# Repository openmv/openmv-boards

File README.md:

# openmv-boards
OpenMV boards, schematics, and layout.

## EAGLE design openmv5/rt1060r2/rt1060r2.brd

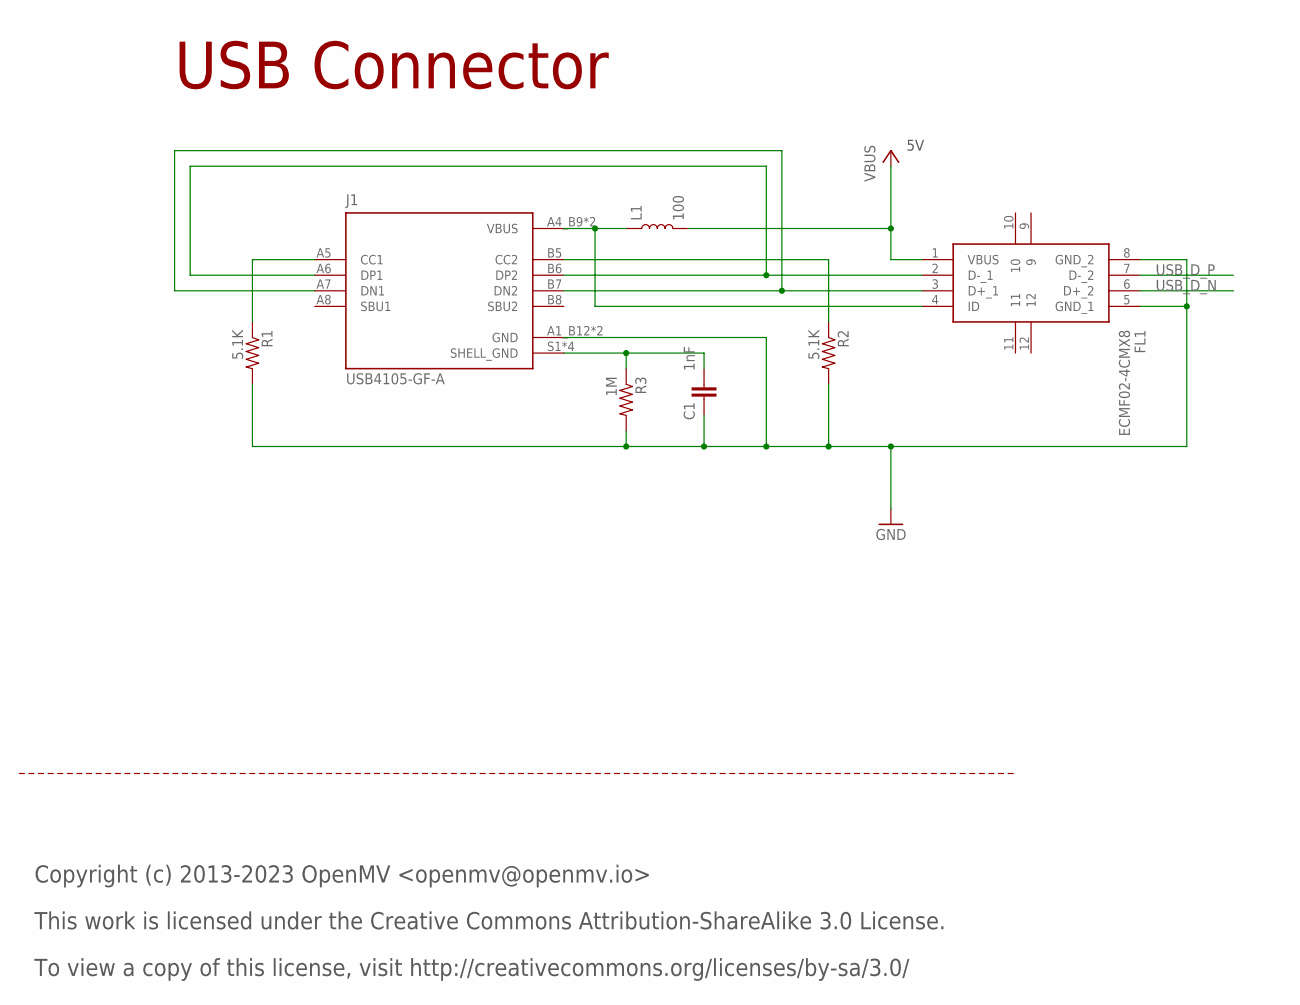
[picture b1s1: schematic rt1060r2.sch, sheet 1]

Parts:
C1: 1nF; 0402; MPN VJ0402Y102JXACW1BC
FL1: ECMF02-4CMX8; ECMF024CMX8; MPN ECMF02-4CMX8
J1: USB4105-GF-A; GCT_USB4105-GF-A; MPN USB4105-GF-A
L1: 100; 0603; MPN MFBM1V1608-101-R
R1, R2: 5.1K; 0402; MPN RC0402JR-075K1L
R3: 1M; 0402; MPN CRCW04021M00FKEDC

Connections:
CC1: J1.A5 (CC1), R1.1
CC2: J1.B5 (CC2), R2.1
D_N: FL1.3 (D+_1), J1.A7 (DN1), J1.B7 (DN2)
D_P: FL1.2 (D-_1), J1.A6 (DP1), J1.B6 (DP2)
GND: C1.1, FL1.5 (GND_1), FL1.8 (GND_2), J1.A1_B12 (GND), J1.B1_A12 (GND), R1.2, R2.2, R3.2; also elsewhere on the board
SHELL_GND: C1.2, J1.S1 (SHELL_GND), J1.S2 (SHELL_GND), J1.S3 (SHELL_GND), J1.S4 (SHELL_GND), R3.1
USB_D_N: FL1.6 (D+_2); also elsewhere on the board
USB_D_P: FL1.7 (D-_2); also elsewhere on the board
USB_VBUS: FL1.4 (ID), J1.A4_B9 (VBUS), J1.B4_A9 (VBUS), L1.1
VBUS: FL1.1 (VBUS), L1.2; also elsewhere on the board

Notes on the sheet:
USB Connector
Copyright (c) 2013-2023 OpenMV <openmv@openmv.io>
This work is licensed under the Creative Commons Attribution-ShareAlike 3.0 License.
To view a copy of this license, visit http://creativecommons.org/licenses/by-sa/3.0/

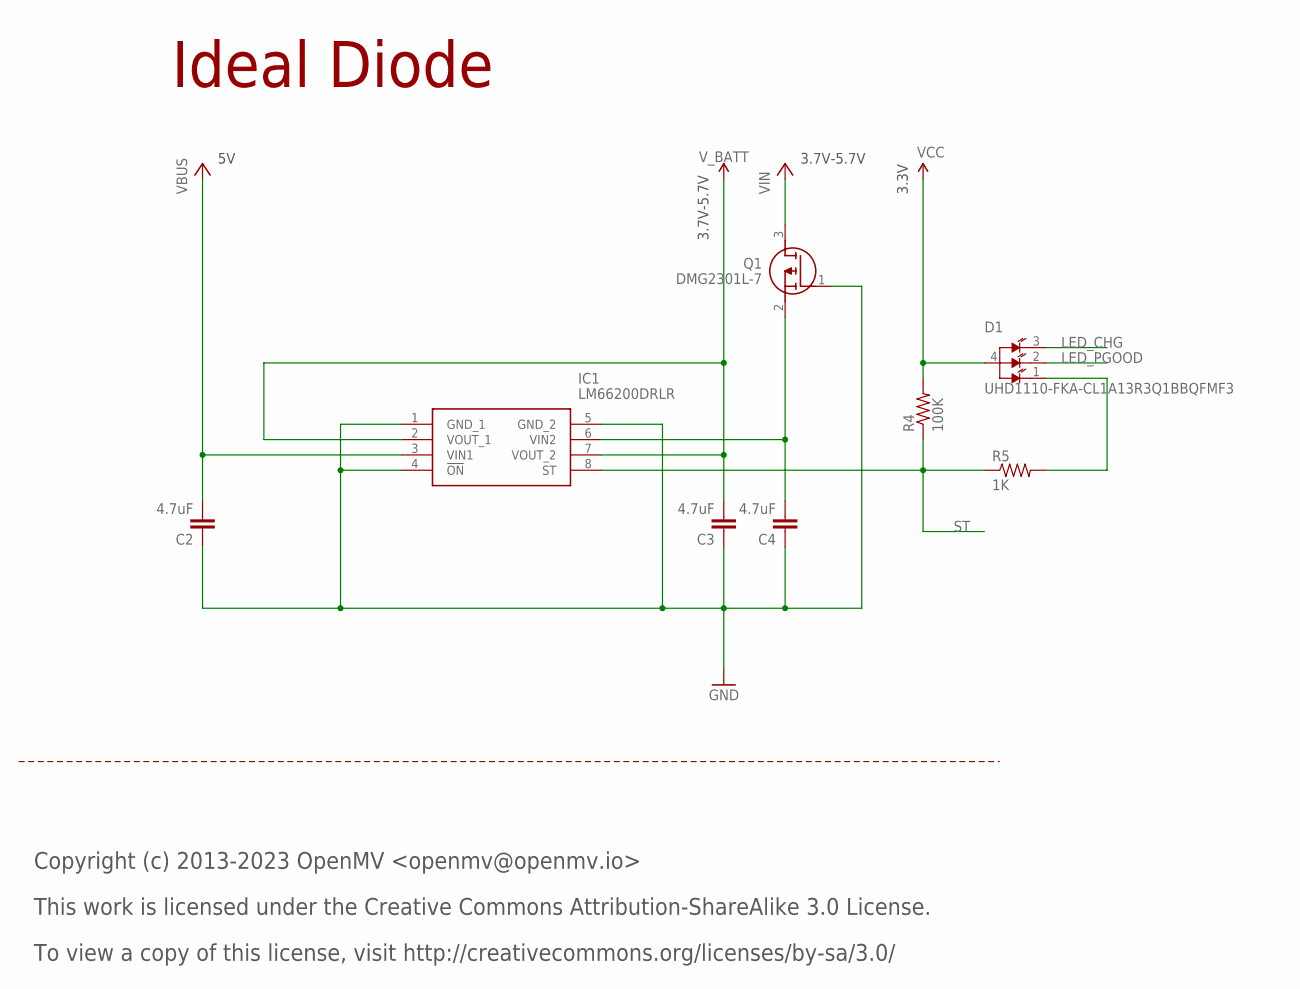
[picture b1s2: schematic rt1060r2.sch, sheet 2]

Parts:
C2, C3, C4: 4.7uF; 0402; MPN JMK105BBJ475MV-F
D1: UHD1110-FKA-CL1A13R3Q1BBQFMF3; LED_UHD1110-FKA-CL1A13R3Q1BBQFMF3; MPN UHD1110-FKA-CL1A13r3q1BBQFMF3
IC1: LM66200DRLR; SOTFL50P160X60-8N; MPN LM66200DRLR
Q1: DMG2301L-7; SOT96P240X110-3N; MPN DMG2301L-7
R4: 100K; 0402; MPN AC0402FR-07100KL
R5: 1K; 0402; MPN CRCW04021K00FKEDC

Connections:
GND: C2.1, C3.1, C4.1, IC1.1 (GND_1), IC1.4 (!ON), IC1.5 (GND_2), Q1.1 (G); also elsewhere on the board
LED_CHG: D1.3 (RED); also elsewhere on the board
LED_PGOOD: D1.2 (GREEN); also elsewhere on the board
LED_ST: D1.1 (BLUE), R5.2
ST: IC1.8 (ST), R4.1, R5.1; also elsewhere on the board
VBUS: C2.2, IC1.3 (VIN1); also elsewhere on the board
VCC: D1.4 (ANODE), R4.2; also elsewhere on the board
VIN: Q1.3 (D); also elsewhere on the board
VIN_INT: C4.2, IC1.6 (VIN2), Q1.2 (S)
V_BATT: C3.2, IC1.2 (VOUT_1), IC1.7 (VOUT_2); also elsewhere on the board

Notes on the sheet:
Copyright (c) 2013-2023 OpenMV <openmv@openmv.io>
This work is licensed under the Creative Commons Attribution-ShareAlike 3.0 License.
To view a copy of this license, visit http://creativecommons.org/licenses/by-sa/3.0/
Ideal Diode
3.7V-5.7V
3.3V

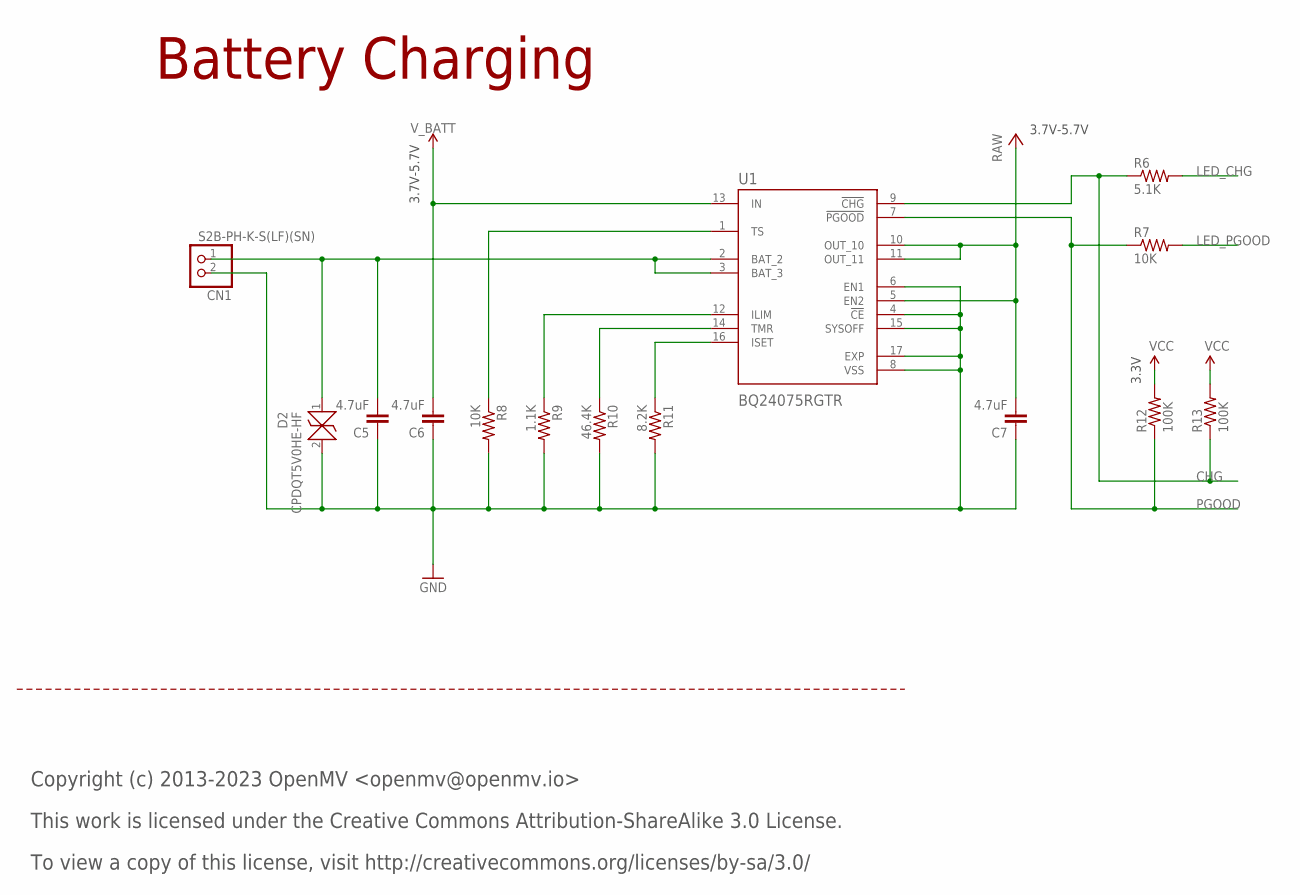
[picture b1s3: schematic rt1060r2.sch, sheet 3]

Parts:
C5, C6, C7: 4.7uF; 0402; MPN JMK105BBJ475MV-F
CN1: S2B-PH-K-S(LF)(SN); JST-PH-2-THM-RA; MPN S2B-PH-K-S(LF)(SN)
D2: CPDQT5V0HE-HF; CPDQT5V0HEHF; MPN CPDQT5V0HE-HF
R6: 5.1K; 0402; MPN RC0402JR-075K1L
R7, R8: 10K; 0402; MPN AC0402FR-1310KL
R9: 1.1K; 0402; MPN RC0402JR-071K1L
R10: 46.4K; 0402; MPN WR04X4642FTL
R11: 8.2K; 0402; MPN CR0402-FX-8201GLF
R12, R13: 100K; 0402; MPN AC0402FR-07100KL
U1: BQ24075RGTR; QFN50P300X300X100-17N; MPN BQ24075RGTR

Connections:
BAT: C5.2, CN1.1 (2), D2.1, U1.2 (BAT_2), U1.3 (BAT_3)
CHG: R6.1, R13.1, U1.9 (!CHG); also elsewhere on the board
GND: C5.1, C6.1, C7.1, CN1.2 (1), D2.2, R8.2, R9.2, R10.2, R11.2, U1.4 (!CE), U1.6 (EN1), U1.8 (VSS), U1.15 (SYSOFF), U1.17 (EXP); also elsewhere on the board
ILIM: R9.1, U1.12 (ILIM)
ISET: R11.1, U1.16 (ISET)
LED_CHG: R6.2; also elsewhere on the board
LED_PGOOD: R7.2; also elsewhere on the board
PGOOD: R7.1, R12.1, U1.7 (!PGOOD); also elsewhere on the board
RAW: C7.2, U1.5 (EN2), U1.10 (OUT_10), U1.11 (OUT_11); also elsewhere on the board
TMR: R10.1, U1.14 (TMR)
TS: R8.1, U1.1 (TS)
VCC: R12.2, R13.2; also elsewhere on the board
V_BATT: C6.2, U1.13 (IN); also elsewhere on the board

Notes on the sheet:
Copyright (c) 2013-2023 OpenMV <openmv@openmv.io>
This work is licensed under the Creative Commons Attribution-ShareAlike 3.0 License.
To view a copy of this license, visit http://creativecommons.org/licenses/by-sa/3.0/
Battery Charging
3.7V-5.7V
3.3V

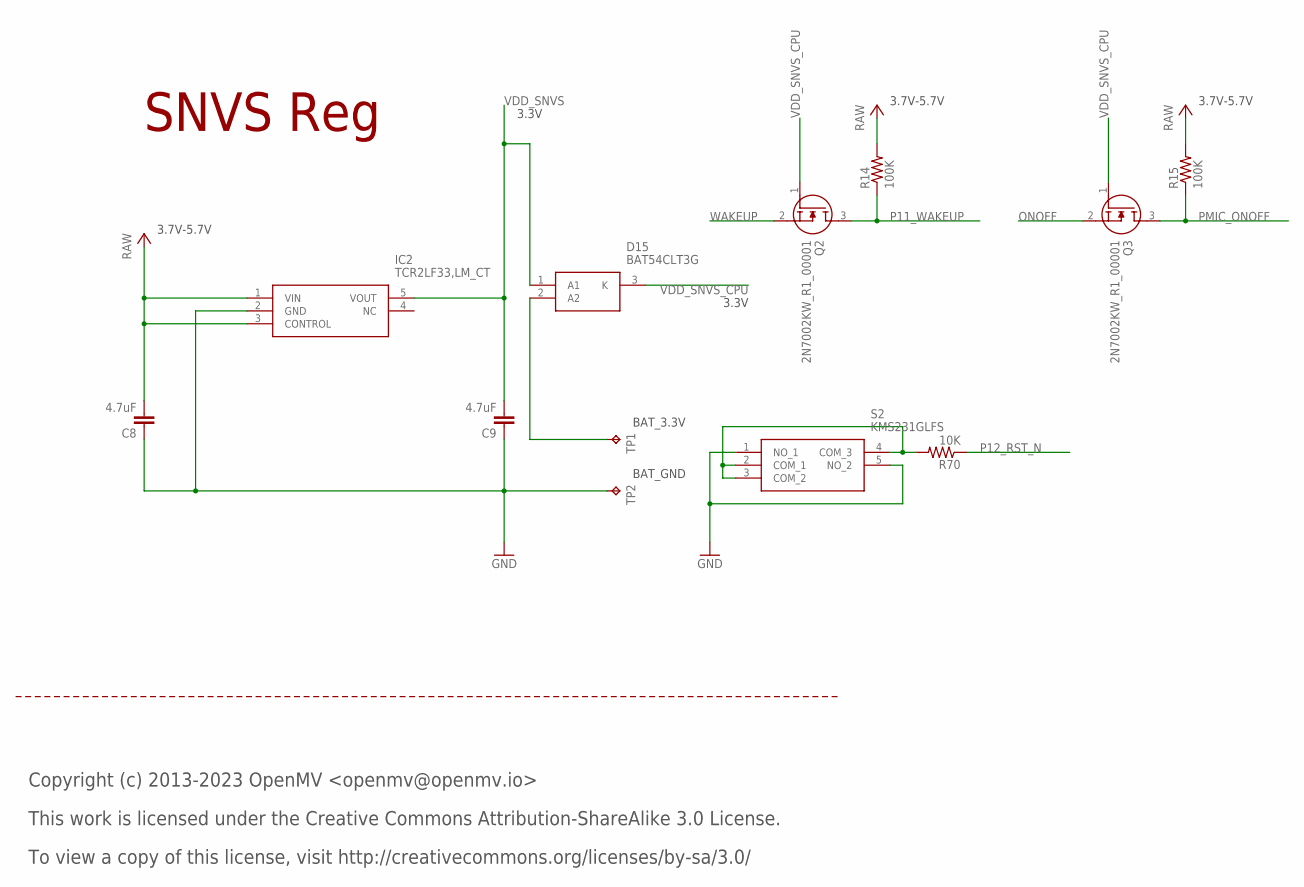
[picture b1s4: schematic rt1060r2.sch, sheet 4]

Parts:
C8, C9: 4.7uF; 0402; MPN JMK105BBJ475MV-F
D15: BAT54CLT3G; SOT96P237X111-3N
IC2: TCR2LF33,LM_CT; TCR2LF33LMCT; MPN TCR2LF33,LM(CT
Q2, Q3: 2N7002KW_R1_00001; SOT65P210X110-3N; MPN 2N7002KW_R1_00001
R14, R15: 100K; 0402; MPN AC0402FR-07100KL
R70: 10K; 0402; MPN AC0402FR-1310KL
S2: KMS231GLFS; MPN KMS231GLFS
TP1, TP2: TPTP10R; TP10R

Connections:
GND: C8.1, C9.1, IC2.2 (GND), S2.1 (NO_1), S2.5 (NO_2), TP2.TP; also elsewhere on the board
ONOFF: Q3.2 (S); also elsewhere on the board
P11_WAKEUP: Q2.3 (D), R14.1; also elsewhere on the board
P12_RST_N: R70.1; also elsewhere on the board
PMIC_ONOFF: Q3.3 (D), R15.1; also elsewhere on the board
RAW: C8.2, IC2.1 (VIN), IC2.3 (CONTROL), R14.2, R15.2; also elsewhere on the board
RST_BUTTON: R70.2, S2.2 (COM_1), S2.3 (COM_2), S2.4 (COM_3)
SNVS_BAT: D15.2 (A2), TP1.TP
VDD_SNVS: C9.2, D15.1 (A1), IC2.5 (VOUT)
VDD_SNVS_CPU: D15.3 (K), Q2.1 (G), Q3.1 (G); also elsewhere on the board
WAKEUP: Q2.2 (S); also elsewhere on the board

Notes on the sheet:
Copyright (c) 2013-2023 OpenMV <openmv@openmv.io>
This work is licensed under the Creative Commons Attribution-ShareAlike 3.0 License.
To view a copy of this license, visit http://creativecommons.org/licenses/by-sa/3.0/
SNVS Reg
3.7V-5.7V
3.3V
BAT_3.3V
BAT_GND

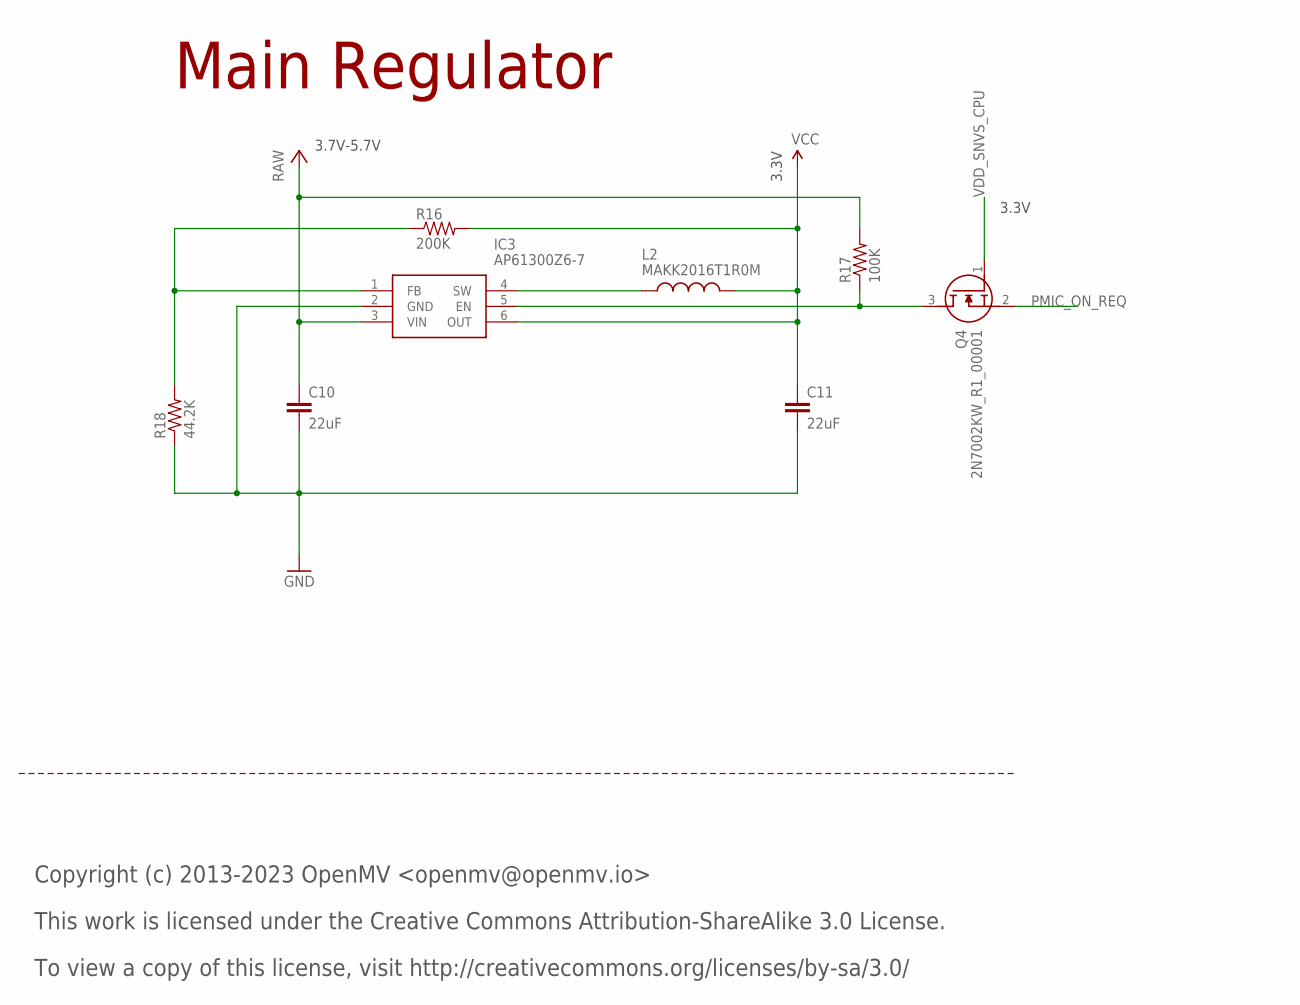
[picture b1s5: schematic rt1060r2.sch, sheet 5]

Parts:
C10, C11: 22uF; 0805; MPN CL21A226MQQNNNE
IC3: AP61300Z6-7; SOTFL50P162X60-6N; MPN AP61300Z6-7
L2: MAKK2016T1R0M; INDC2016X100N; MPN MAKK2016T1R0M
Q4: 2N7002KW_R1_00001; SOT65P210X110-3N; MPN 2N7002KW_R1_00001
R16: 200K; 0402; MPN CRCW0402200KFKEDC
R17: 100K; 0402; MPN AC0402FR-07100KL
R18: 44.2K; 0402; MPN AC0402FR-0744K2L

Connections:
EN: IC3.5 (EN), Q4.3 (D), R17.1
FB: IC3.1 (FB), R16.1, R18.2
GND: C10.2, C11.2, IC3.2 (GND), R18.1; also elsewhere on the board
PMIC_ON_REQ: Q4.2 (S); also elsewhere on the board
RAW: C10.1, IC3.3 (VIN), R17.2; also elsewhere on the board
SW: IC3.4 (SW), L2.1
VCC: C11.1, IC3.6 (OUT), L2.2, R16.2; also elsewhere on the board
VDD_SNVS_CPU: Q4.1 (G); also elsewhere on the board

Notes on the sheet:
Copyright (c) 2013-2023 OpenMV <openmv@openmv.io>
This work is licensed under the Creative Commons Attribution-ShareAlike 3.0 License.
To view a copy of this license, visit http://creativecommons.org/licenses/by-sa/3.0/
Main Regulator
3.7V-5.7V
3.3V

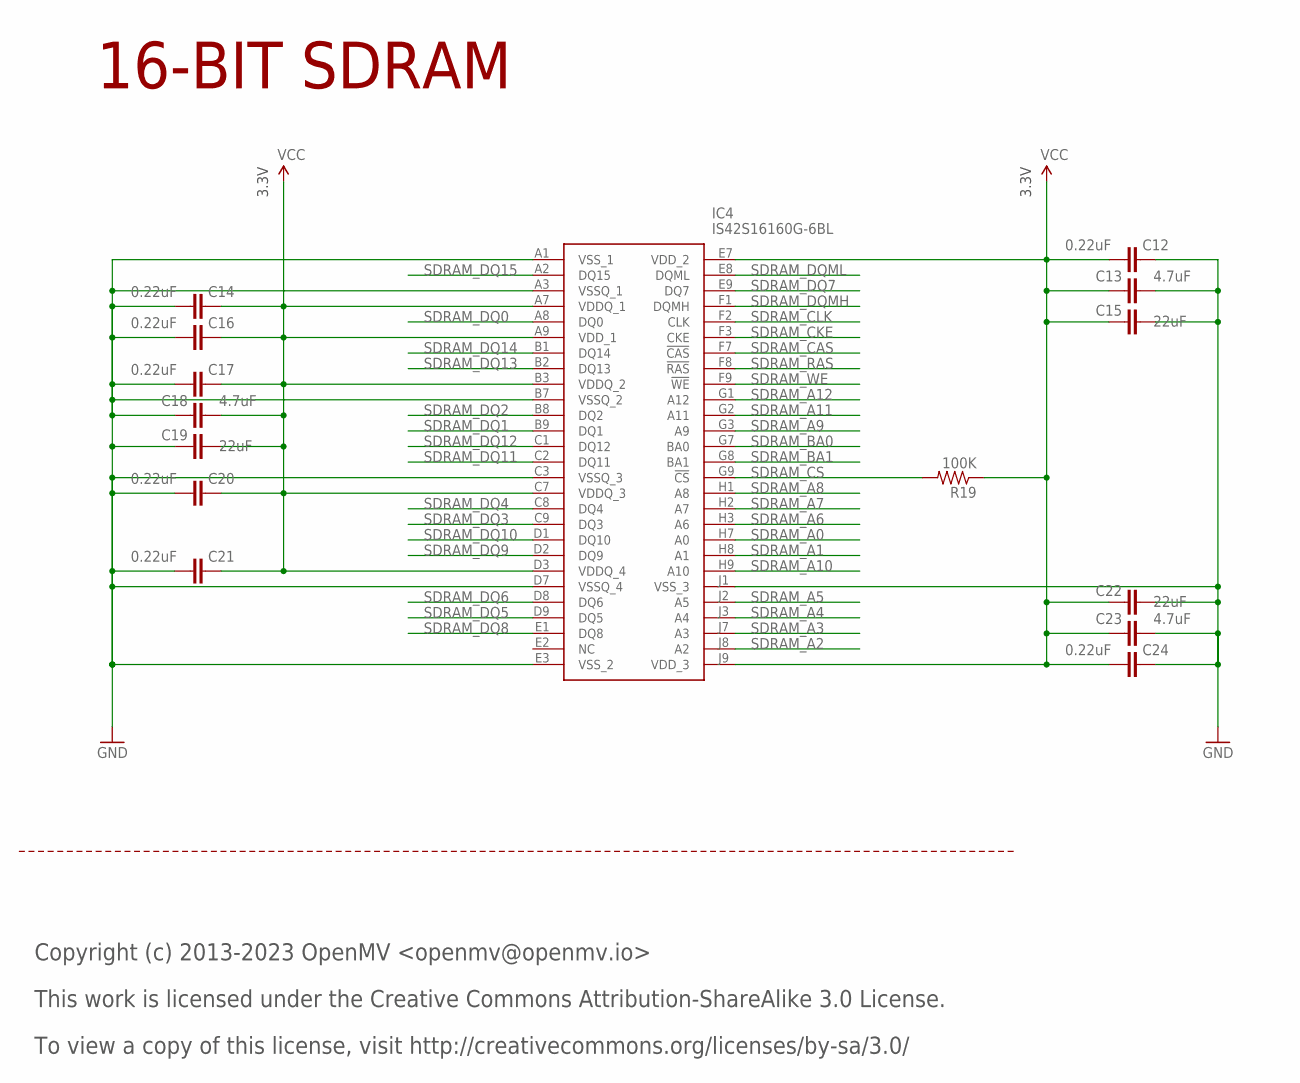
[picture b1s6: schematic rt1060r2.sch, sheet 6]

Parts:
C12, C14, C16, C17, C20, C21, C24: 0.22uF; C0201; MPN GRM033R60J224ME15D
C13, C18, C23: 4.7uF; 0402; MPN JMK105BBJ475MV-F
C15, C19, C22: 22uF; 0805; MPN CL21A226MQQNNNE
IC4: IS42S16160G-6BL; BGA54C80P9X9_800X800X120; MPN IS42S16160G-6BL
R19: 100K; 0402; MPN AC0402FR-07100KL

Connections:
GND: C12.1, C13.2, C14.2, C15.2, C16.2, C17.2, C18.1, C19.1, C20.2, C21.2, C22.2, C23.2, C24.1, IC4.A1 (VSS_1), IC4.A3 (VSSQ_1), IC4.B7 (VSSQ_2), IC4.C3 (VSSQ_3), IC4.D7 (VSSQ_4), IC4.E3 (VSS_2), IC4.J1 (VSS_3); also elsewhere on the board
SDRAM_A0: IC4.H7 (A0); also elsewhere on the board
SDRAM_A1: IC4.H8 (A1); also elsewhere on the board
SDRAM_A2: IC4.J8 (A2); also elsewhere on the board
SDRAM_A3: IC4.J7 (A3); also elsewhere on the board
SDRAM_A4: IC4.J3 (A4); also elsewhere on the board
SDRAM_A5: IC4.J2 (A5); also elsewhere on the board
SDRAM_A6: IC4.H3 (A6); also elsewhere on the board
SDRAM_A7: IC4.H2 (A7); also elsewhere on the board
SDRAM_A8: IC4.H1 (A8); also elsewhere on the board
SDRAM_A9: IC4.G3 (A9); also elsewhere on the board
SDRAM_A10: IC4.H9 (A10); also elsewhere on the board
SDRAM_A11: IC4.G2 (A11); also elsewhere on the board
SDRAM_A12: IC4.G1 (A12); also elsewhere on the board
SDRAM_BA0: IC4.G7 (BA0); also elsewhere on the board
SDRAM_BA1: IC4.G8 (BA1); also elsewhere on the board
SDRAM_CAS: IC4.F7 (!CAS); also elsewhere on the board
SDRAM_CKE: IC4.F3 (CKE); also elsewhere on the board
SDRAM_CLK: IC4.F2 (CLK); also elsewhere on the board
SDRAM_CS: IC4.G9 (!CS), R19.2; also elsewhere on the board
SDRAM_DQ0: IC4.A8 (DQ0); also elsewhere on the board
SDRAM_DQ1: IC4.B9 (DQ1); also elsewhere on the board
SDRAM_DQ2: IC4.B8 (DQ2); also elsewhere on the board
SDRAM_DQ3: IC4.C9 (DQ3); also elsewhere on the board
SDRAM_DQ4: IC4.C8 (DQ4); also elsewhere on the board
SDRAM_DQ5: IC4.D9 (DQ5); also elsewhere on the board
SDRAM_DQ6: IC4.D8 (DQ6); also elsewhere on the board
SDRAM_DQ7: IC4.E9 (DQ7); also elsewhere on the board
SDRAM_DQ8: IC4.E1 (DQ8); also elsewhere on the board
SDRAM_DQ9: IC4.D2 (DQ9); also elsewhere on the board
SDRAM_DQ10: IC4.D1 (DQ10); also elsewhere on the board
SDRAM_DQ11: IC4.C2 (DQ11); also elsewhere on the board
SDRAM_DQ12: IC4.C1 (DQ12); also elsewhere on the board
SDRAM_DQ13: IC4.B2 (DQ13); also elsewhere on the board
SDRAM_DQ14: IC4.B1 (DQ14); also elsewhere on the board
SDRAM_DQ15: IC4.A2 (DQ15); also elsewhere on the board
SDRAM_DQMH: IC4.F1 (DQMH); also elsewhere on the board
SDRAM_DQML: IC4.E8 (DQML); also elsewhere on the board
SDRAM_RAS: IC4.F8 (!RAS); also elsewhere on the board
SDRAM_WE: IC4.F9 (!WE); also elsewhere on the board
VCC: C12.2, C13.1, C14.1, C15.1, C16.1, C17.1, C18.2, C19.2, C20.1, C21.1, C22.1, C23.1, C24.2, IC4.A7 (VDDQ_1), IC4.A9 (VDD_1), IC4.B3 (VDDQ_2), IC4.C7 (VDDQ_3), IC4.D3 (VDDQ_4), IC4.E7 (VDD_2), IC4.J9 (VDD_3), R19.1; also elsewhere on the board

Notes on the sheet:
Copyright (c) 2013-2023 OpenMV <openmv@openmv.io>
This work is licensed under the Creative Commons Attribution-ShareAlike 3.0 License.
To view a copy of this license, visit http://creativecommons.org/licenses/by-sa/3.0/
16-BIT SDRAM
3.3V

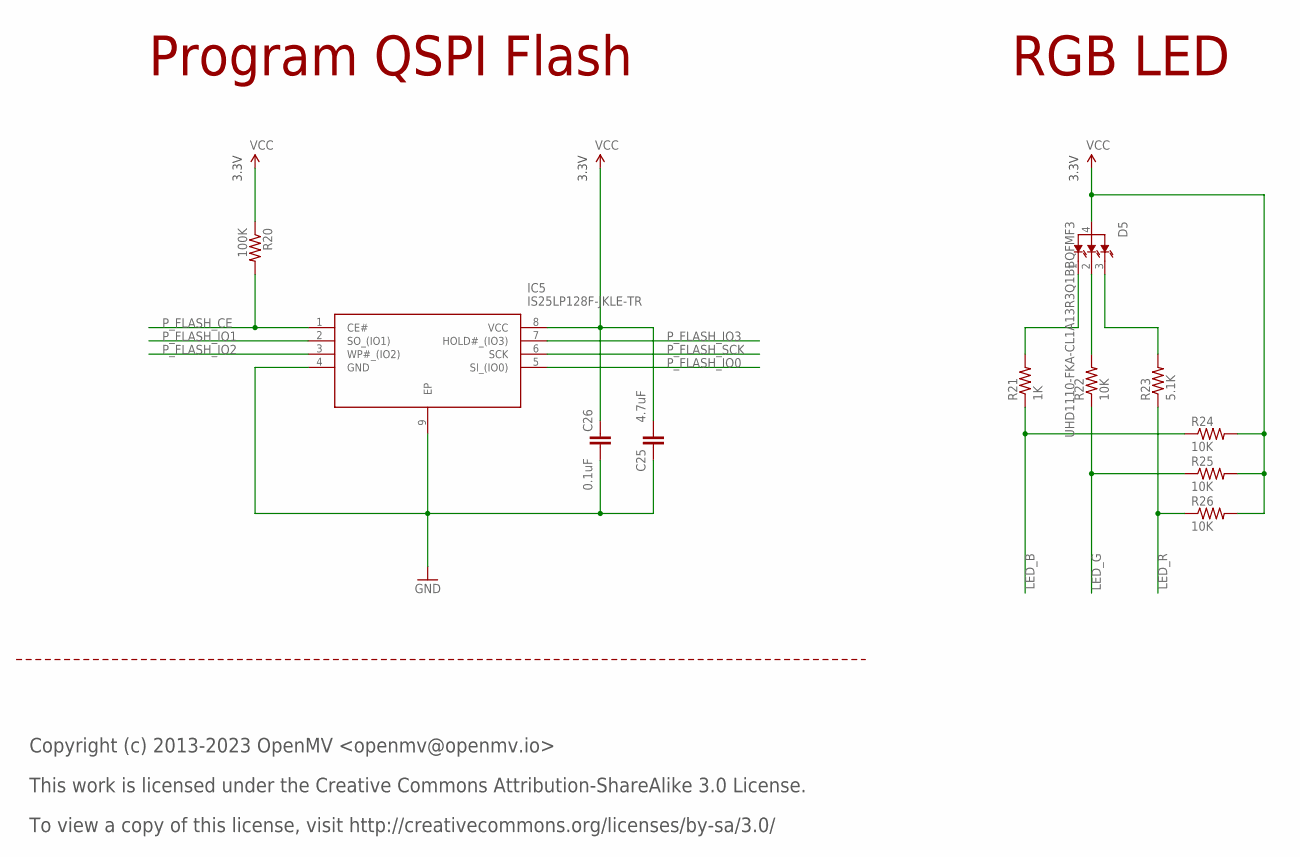
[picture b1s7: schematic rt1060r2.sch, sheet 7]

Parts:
C25: 4.7uF; 0402; MPN JMK105BBJ475MV-F
C26: 0.1uF; 0402; MPN C0402C104Z4VAC
D5: UHD1110-FKA-CL1A13R3Q1BBQFMF3; LED_UHD1110-FKA-CL1A13R3Q1BBQFMF3; MPN UHD1110-FKA-CL1A13r3q1BBQFMF3
IC5: IS25LP128F-JKLE-TR; SON127P500X595X80-9N; MANUFACTURER_PART_NUMBER IS25LP128F-JKLE-TR; MOUSER_PART_NUMBER 870-5LP128F-JKLE-TR
R20: 100K; 0402; MPN AC0402FR-07100KL
R21: 1K; 0402; MPN CRCW04021K00FKEDC
R22, R24, R25, R26: 10K; 0402; MPN AC0402FR-1310KL
R23: 5.1K; 0402; MPN RC0402JR-075K1L

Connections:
GND: C25.1, C26.2, IC5.4 (GND), IC5.9 (EP); also elsewhere on the board
LED_B: R21.1, R24.1; also elsewhere on the board
LED_B_INT: D5.1 (BLUE), R21.2
LED_G: R22.1, R25.1; also elsewhere on the board
LED_G_INT: D5.2 (GREEN), R22.2
LED_R: R23.1, R26.1; also elsewhere on the board
LED_R_INT: D5.3 (RED), R23.2
P_FLASH_CE: IC5.1 (CE#), R20.2; also elsewhere on the board
P_FLASH_IO0: IC5.5 (SI_(IO0)); also elsewhere on the board
P_FLASH_IO1: IC5.2 (SO_(IO1)); also elsewhere on the board
P_FLASH_IO2: IC5.3 (WP#_(IO2)); also elsewhere on the board
P_FLASH_IO3: IC5.7 (HOLD#_(IO3)); also elsewhere on the board
P_FLASH_SCK: IC5.6 (SCK); also elsewhere on the board
VCC: C25.2, C26.1, D5.4 (ANODE), IC5.8 (VCC), R20.1, R24.2, R25.2, R26.2; also elsewhere on the board

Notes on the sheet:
Copyright (c) 2013-2023 OpenMV <openmv@openmv.io>
This work is licensed under the Creative Commons Attribution-ShareAlike 3.0 License.
To view a copy of this license, visit http://creativecommons.org/licenses/by-sa/3.0/
Program QSPI Flash
RGB LED
3.3V

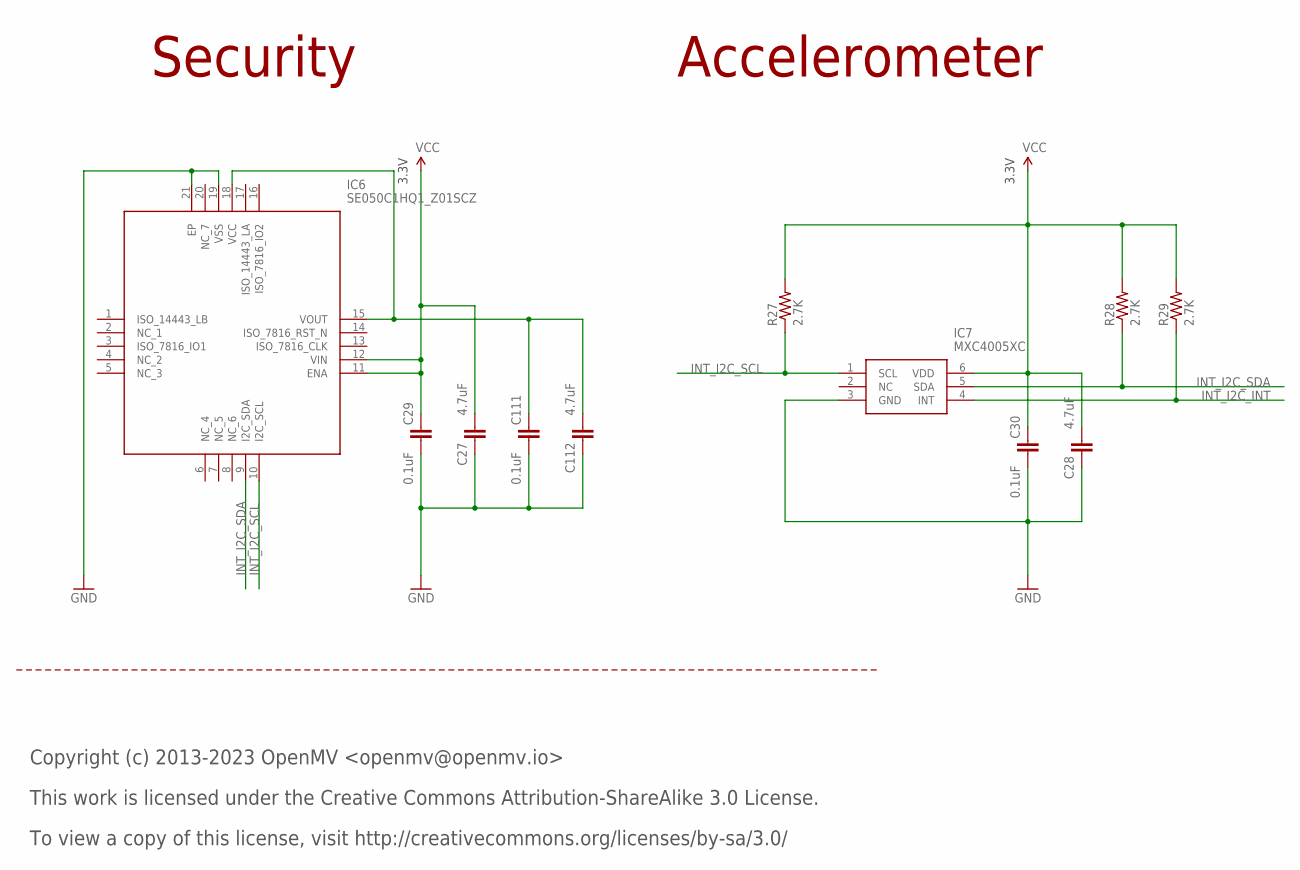
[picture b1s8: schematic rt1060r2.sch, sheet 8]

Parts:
C27, C28, C112: 4.7uF; 0402; MPN JMK105BBJ475MV-F
C29, C30, C111: 0.1uF; 0402; MPN C0402C104Z4VAC
IC6: SE050C1HQ1_Z01SCZ; QFN40P300X300X33-21N; MPN SE050C1HQ1/Z01SCZ
IC7: MXC4005XC; MPN MXC4005XC
R27, R28, R29: 2.7K; 0402; MPN AC0402JR-072K7L

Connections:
C_VOUT: C111.1, C112.2, IC6.15 (VOUT), IC6.18 (VCC)
GND: C27.1, C28.1, C29.2, C30.2, C111.2, C112.1, IC6.19 (VSS), IC6.21 (EP), IC7.3 (GND); also elsewhere on the board
INT_I2C_INT: IC7.4 (INT), R29.1; also elsewhere on the board
INT_I2C_SCL: IC6.10 (I2C_SCL), IC7.1 (SCL), R27.1; also elsewhere on the board
INT_I2C_SDA: IC6.9 (I2C_SDA), IC7.5 (SDA), R28.1; also elsewhere on the board
VCC: C27.2, C28.2, C29.1, C30.1, IC6.11 (ENA), IC6.12 (VIN), IC7.6 (VDD), R27.2, R28.2, R29.2; also elsewhere on the board

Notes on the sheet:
Copyright (c) 2013-2023 OpenMV <openmv@openmv.io>
This work is licensed under the Creative Commons Attribution-ShareAlike 3.0 License.
To view a copy of this license, visit http://creativecommons.org/licenses/by-sa/3.0/
Security
Accelerometer
3.3V

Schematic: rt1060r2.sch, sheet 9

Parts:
C31: 4.7uF; 0402; MPN JMK105BBJ475MV-F
C32: 22uF; 0805; MPN CL21A226MQQNNNE
C33: 0.1uF; 0402; MPN C0402C104Z4VAC
D6, D7: CPDQT5V0HE-HF; CPDQT5V0HEHF; MPN CPDQT5V0HE-HF
FL2: EMIF06-1005M12; SON40P150X250X65-13N; MPN EMIF06-1005M12
J2: USD-1040310811; 1040310811; MPN 104031-0811
R30, R31, R32, R33, R34, R35: 100K; 0402; MPN AC0402FR-07100KL

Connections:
GND: C31.1, C32.2, C33.2, D6.2, D7.2, FL2.13 (EP), J2.CD$2 (CD_POL), J2.G$1 (SHD), J2.G$2 (SHD), J2.G$3 (SHD), J2.G$4 (SHD), J2.P$6 (VSS); also elsewhere on the board
SD_CD: D7.1, J2.CD$1 (CD), R30.1; also elsewhere on the board
SD_CLK: FL2.4 (INPUT_4); also elsewhere on the board
SD_CLK_INT: FL2.9 (OUTPUT_4), J2.P$5 (CLK)
SD_CMD: FL2.3 (INPUT_3), R33.1; also elsewhere on the board
SD_CMD_INT: FL2.10 (OUTPUT_3), J2.P$3 (CMD)
SD_DAT0: FL2.5 (INPUT_5), R32.1; also elsewhere on the board
SD_DAT0_INT: FL2.8 (OUTPUT_5), J2.P$7 (DAT0)
SD_DAT1: FL2.6 (INPUT_6), R31.1; also elsewhere on the board
SD_DAT1_INT: FL2.7 (OUTPUT_6), J2.P$8 (DAT1)
SD_DAT2: FL2.1 (INPUT_1), R35.1; also elsewhere on the board
SD_DAT2_INT: FL2.12 (OUTPUT_1), J2.P$1 (DAT2)
SD_DAT3: FL2.2 (INPUT_2), R34.1; also elsewhere on the board
SD_DAT3_INT: FL2.11 (OUTPUT_2), J2.P$2 (DAT3/CD)
VCC: C31.2, C32.1, C33.1, D6.1, J2.P$4 (VDD), R30.2, R31.2, R32.2, R33.2, R34.2, R35.2; also elsewhere on the board

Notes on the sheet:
Copyright (c) 2013-2023 OpenMV <openmv@openmv.io>
This work is licensed under the Creative Commons Attribution-ShareAlike 3.0 License.
To view a copy of this license, visit http://creativecommons.org/licenses/by-sa/3.0/
SD CARD
3.3V

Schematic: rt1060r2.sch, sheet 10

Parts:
C34, C40: 22uF; 0805; MPN CL21A226MQQNNNE
C35, C36, C37, C38, C39, C41: 4.7uF; 0402; MPN JMK105BBJ475MV-F
J3: DF12-36-DS; MPN DF12NB(3.0)-36DS-0.5V(51)
L3: 100; 0402; MPN MFBM1V1005-101-R
R36, R41: 100K; 0402; MPN AC0402FR-07100KL
R37, R38: 10K; 0402; MPN AC0402FR-1310KL
R39, R40: 4.7K; 0402; MPN AC0402FR-074K7L
R42, R43: 1K; 0402; MPN CRCW04021K00FKEDC

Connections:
DCMI_CLK: J3.12; also elsewhere on the board
DCMI_D0: J3.31; also elsewhere on the board
DCMI_D1: J3.29; also elsewhere on the board
DCMI_D2: J3.35; also elsewhere on the board
DCMI_D3: J3.28; also elsewhere on the board
DCMI_D4: J3.26; also elsewhere on the board
DCMI_D5: J3.33; also elsewhere on the board
DCMI_D6: J3.24; also elsewhere on the board
DCMI_D7: J3.22; also elsewhere on the board
DCMI_FSIN: J3.23, R42.1
DCMI_HSYNC: J3.18; also elsewhere on the board
DCMI_MISO: J3.15; also elsewhere on the board
DCMI_MOSI: J3.17; also elsewhere on the board
DCMI_PCLK: J3.14; also elsewhere on the board
DCMI_PWDN: J3.25, R38.1; also elsewhere on the board
DCMI_RST: J3.21, R37.1; also elsewhere on the board
DCMI_SCL: J3.32, R39.1; also elsewhere on the board
DCMI_SCLK: J3.13; also elsewhere on the board
DCMI_SDA: J3.34, R40.1; also elsewhere on the board
DCMI_SSEL: J3.11, R36.1; also elsewhere on the board
DCMI_VSYNC: J3.16; also elsewhere on the board
GND: C34.2, C35.1, C36.1, C37.1, C38.1, C39.1, C40.2, C41.1, J3.5, J3.19, J3.27, R37.2; also elsewhere on the board
P10_PWM: R43.1; also elsewhere on the board
PWM_FSIN: R41.1, R42.2, R43.2; also elsewhere on the board
VCC: C34.1, C35.2, C36.2, C37.2, C38.2, C39.2, J3.2, J3.10, J3.20, J3.30, J3.36, L3.2, R36.2, R38.2, R39.2, R40.2, R41.2; also elsewhere on the board
VDDA: C40.1, C41.2, J3.4, L3.1

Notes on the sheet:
Copyright (c) 2013-2023 OpenMV <openmv@openmv.io>
This work is licensed under the Creative Commons Attribution-ShareAlike 3.0 License.
To view a copy of this license, visit http://creativecommons.org/licenses/by-sa/3.0/
IMAGE SENSOR CONNECTOR
3.3V

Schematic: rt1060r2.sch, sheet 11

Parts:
D8, D9, D10, D11, D12, D13: CPDQT5V0HE-HF; CPDQT5V0HEHF; MPN CPDQT5V0HE-HF
FL3, FL4: EMIF06-1005M12; SON40P150X250X65-13N; MPN EMIF06-1005M12
J4, J5, J6, J7: DNP; 1X08
R44, R45: 0; 0402; MPN RC0402JR-070RL
R46: 10K; 0402; MPN AC0402FR-1310KL

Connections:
DCMI_D7: R46.1; also elsewhere on the board
GND: D8.2, D9.2, D10.2, D11.2, D12.2, D13.2, FL3.13 (EP), FL4.13 (EP), J5.1, J7.1; also elsewhere on the board
JTAG_TDI_INT: R44.1; also elsewhere on the board
JTAG_TRSTB_INT: R45.1; also elsewhere on the board
MDI_LED: J5.8; also elsewhere on the board
MDI_RX_N: J5.7; also elsewhere on the board
MDI_RX_P: J5.6; also elsewhere on the board
MDI_TX_N: J5.5; also elsewhere on the board
MDI_TX_P: J5.4; also elsewhere on the board
P0_MOSI: FL3.1 (INPUT_1); also elsewhere on the board
P0_MOSI_INT: FL3.12 (OUTPUT_1), J4.8
P1_MISO: FL3.2 (INPUT_2); also elsewhere on the board
P1_MISO_INT: FL3.11 (OUTPUT_2), J4.7
P2_SCLK: FL3.3 (INPUT_3); also elsewhere on the board
P2_SCLK_INT: FL3.10 (OUTPUT_3), J4.6
P3_NSS: FL3.4 (INPUT_4); also elsewhere on the board
P3_NSS_INT: FL3.9 (OUTPUT_4), J4.5
P4_SCL: FL3.5 (INPUT_5); also elsewhere on the board
P4_SCL_INT: FL3.8 (OUTPUT_5), J4.4
P5_SDA: FL3.6 (INPUT_6); also elsewhere on the board
P5_SDA_INT: FL3.7 (OUTPUT_6), J4.3
P6_ADC: FL4.1 (INPUT_1); also elsewhere on the board
P6_ADC_INT: FL4.12 (OUTPUT_1), J4.2
P7_PWM: FL4.2 (INPUT_2); also elsewhere on the board
P7_PWM_INT: FL4.11 (OUTPUT_2), J7.3
P8_PWM: FL4.3 (INPUT_3); also elsewhere on the board
P8_PWM_INT: FL4.10 (OUTPUT_3), J7.4
P9_PWM: FL4.4 (INPUT_4); also elsewhere on the board
P9_PWM_INT: FL4.9 (OUTPUT_4), J7.5
P10_PWM: FL4.5 (INPUT_5); also elsewhere on the board
P10_PWM_INT: FL4.8 (OUTPUT_5), J7.6
P11_WAKEUP: FL4.6 (INPUT_6); also elsewhere on the board
P11_WAKEUP_INT: FL4.7 (OUTPUT_6), J7.7
P12_RST_N_EXT: J7.8; also elsewhere on the board
P13: J6.3, R45.2
P14: J6.4, R44.2
PMIC_ONOFF: D11.1, J5.3; also elsewhere on the board
RAW: D9.1, J5.2; also elsewhere on the board
SBL: D13.1, J6.2, R46.2
VCC: D8.1, D12.1, J4.1, J6.1; also elsewhere on the board
VIN: D10.1, J7.2; also elsewhere on the board

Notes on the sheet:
Copyright (c) 2013-2023 OpenMV <openmv@openmv.io>
This work is licensed under the Creative Commons Attribution-ShareAlike 3.0 License.
To view a copy of this license, visit http://creativecommons.org/licenses/by-sa/3.0/
I/O HEADERS
3.3V
3.7V-5.7V

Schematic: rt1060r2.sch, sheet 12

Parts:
D14: CPDQT5V0HE-HF; CPDQT5V0HEHF; MPN CPDQT5V0HE-HF
FL5: EMIF06-1005M12; SON40P150X250X65-13N; MPN EMIF06-1005M12
J8: 3221-10-0300-00; CNC_3221-10-0300-00; MPN 3221-10-0300-00
R47: 10K; 0402; MPN AC0402FR-1310KL
R48, R49, R50, R51: DNP; 0402; MPN DNP

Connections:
BT_REG_ON: R47.1; also elsewhere on the board
CHG: R51.2; also elsewhere on the board
GND: D14.2, FL5.13 (EP), J8.3, J8.5, R47.2; also elsewhere on the board
JTAG_TCK: FL5.5 (INPUT_5); also elsewhere on the board
JTAG_TCK_INT: FL5.8 (OUTPUT_5), J8.4
JTAG_TDI: FL5.3 (INPUT_3), R50.1; also elsewhere on the board
JTAG_TDI_INT: FL5.10 (OUTPUT_3), R48.1; also elsewhere on the board
JTAG_TDI_INT_UNUSED: J8.8, R48.2
JTAG_TDO: FL5.4 (INPUT_4); also elsewhere on the board
JTAG_TDO_INT: FL5.9 (OUTPUT_4), J8.6
JTAG_TMS: FL5.6 (INPUT_6); also elsewhere on the board
JTAG_TMS_INT: FL5.7 (OUTPUT_6), J8.2
JTAG_TRSTB: FL5.1 (INPUT_1), R51.1; also elsewhere on the board
JTAG_TRSTB_INT: FL5.12 (OUTPUT_1), R49.1; also elsewhere on the board
JTAG_TRSTB_INT_UNUSED: J8.9, R49.2
P12_RST_N: FL5.2 (INPUT_2); also elsewhere on the board
P12_RST_N_EXT: FL5.11 (OUTPUT_2), J8.10; also elsewhere on the board
ST: R50.2; also elsewhere on the board
VCC: D14.1, J8.1; also elsewhere on the board

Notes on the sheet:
Copyright (c) 2013-2023 OpenMV <openmv@openmv.io>
This work is licensed under the Creative Commons Attribution-ShareAlike 3.0 License.
To view a copy of this license, visit http://creativecommons.org/licenses/by-sa/3.0/
JTAG
3.3V

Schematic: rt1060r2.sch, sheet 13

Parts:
C42, C43, C44, C48: 4.7uF; 0402; MPN JMK105BBJ475MV-F
C45, C49: 22uF; 0805; MPN CL21A226MQQNNNE
C46, C47, C50: 0.1uF; 0402; MPN C0402C104Z4VAC
FD1, FD2, FD3, FD4, FD5, FD6, FD7, FD8: FIDUCIAL1X2; FIDUCIAL-1X2
H1, H2: MOUNT-PAD-ROUND2.8; 2,8-PAD
IC8: KSZ8081RNDCA-TR; QFN50P400X400X90-25N; MPN KSZ8081RNDCA-TR
L4: 100; 0402; MPN MFBM1V1005-101-R
M1, M2: 9774030151R; MPN 9774030151R
R52: 100K; 0402; MPN AC0402FR-07100KL
R53: 220; 0402; MPN CRGCQ0402F220R
R54, R56: 1K; 0402; MPN CRCW04021K00FKEDC
R55: 6.49K; 0402; MPN CR0402-FX-6491GLF

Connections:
ETH_INT: IC8.18 (INTRP), R54.1; also elsewhere on the board
ETH_LED: IC8.23 (LED0_/_ANEN_SPEED), R53.1
ETH_MDC: IC8.11 (MDC); also elsewhere on the board
ETH_MDIO: IC8.10 (MDIO), R56.1; also elsewhere on the board
ETH_RST: C42.2, IC8.24 (RST#), R52.1; also elsewhere on the board
ETH_RXD0: IC8.13 (RXD0); also elsewhere on the board
ETH_RXD1: IC8.12 (RXD1); also elsewhere on the board
ETH_RXDV: IC8.15 (CRS_DV/_PHYAD[1:0]); also elsewhere on the board
ETH_RXERR: IC8.17 (RXER); also elsewhere on the board
ETH_TXCLK: IC8.8 (XI); also elsewhere on the board
ETH_TXD0: IC8.20 (TXD0); also elsewhere on the board
ETH_TXD1: IC8.21 (TXD1); also elsewhere on the board
ETH_TXEN: IC8.19 (TXEN); also elsewhere on the board
ETH_VDDA_3.3: C43.2, C45.1, C46.1, IC8.2 (VDDA_3.3), L4.1
ETH_VDD_1.2: C44.2, C47.1, IC8.1 (VDD_1.2)
GND: C42.1, C43.1, C44.1, C45.2, C46.2, C47.2, C48.1, C49.2, C50.2, IC8.22 (GND_1), IC8.25 (GND_2), R55.2; also elsewhere on the board
MDI_LED: R53.2; also elsewhere on the board
MDI_RX_N: IC8.3 (RXM); also elsewhere on the board
MDI_RX_P: IC8.4 (RXP); also elsewhere on the board
MDI_TX_N: IC8.5 (TXM); also elsewhere on the board
MDI_TX_P: IC8.6 (TXP); also elsewhere on the board
REXT: IC8.9 (REXT), R55.1
VCC: C48.2, C49.1, C50.1, IC8.14 (VDDIO), L4.2, R52.2, R54.2, R56.2; also elsewhere on the board

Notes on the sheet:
Copyright (c) 2013-2023 OpenMV <openmv@openmv.io>
This work is licensed under the Creative Commons Attribution-ShareAlike 3.0 License.
To view a copy of this license, visit http://creativecommons.org/licenses/by-sa/3.0/
Ethernet
Mechanical
3.3V

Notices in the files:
parts and their libraries:
SparkFun-Aesthetics: Licensing: Creative Commons ShareAlike 4.0 International - https://creativecommons.org/licenses/by-sa/4.0
